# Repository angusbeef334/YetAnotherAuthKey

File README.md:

# YetAnotherAuthKey
A Raspberry Pi RP2354 based PCB that can be flashed with the [pico-fido](https://github.com/polhenarejos/pico-fido) firmware to act as a security key similar to Yubikey, because Yubikeys are expensive and I'm broke.

Made for Hack Club [Blueprint](https://blueprint.hackclub.com)

KiCad 9 format, all of the symbol/footprint libraries should be included in the repo. 

RP2350 and related components symbols/footprints were obtained from [Raspberry Pi](https://datasheets.raspberrypi.com/rp2350/Minimal-KiCAD.zip).

LCSC bom (most of these have MOQs)
| Id | Designator                                 | Footprint                                            | Quantity | Designation      | LCSC Part Number | Ext Price USD |
|----|--------------------------------------------|------------------------------------------------------|----------|------------------|------------------|---------------|
| 1  | C8,C12,C10,C11,C17,C15,C19,C18,C14,C16,C13 | C_0402_1005Metric                                    | 11       | 100n             | C1525            | 0.12          |
| 2  | C1,C2                                      | C_0603_1608Metric                                    | 2        | 10u              | C19702           | 0.29          |
| 3  | SW1                                        | SW_Push_SPST_NO_Alps_SKRK                            | 1        | SW_Push          | C115357          | 0.64          |
| 4  | C6,C9,C7,C5                                | C_0402_1005Metric                                    | 4        | 4.7u             | C368809          | 0.31          |
| 5  | U2                                         | SOT-23                                               | 1        | MCP1700x-330xxTT | C39051           | 1.98          |
| 6  | R3,R2                                      | R_0402_1005Metric                                    | 2        | 27               | C138021          | 0.07          |
| 7  | Y1                                         | Crystal_SMD_3225-4Pin_3.2x2.5mm                      | 1        | ABM8-272-T3      | C20625731        | 1.77          |
| 8  | J1                                         | USB_A_Molex_48037-2200_Horizontal                    | 1        | USB_A            | C2681564         | 0.65          |
| 9  | L1                                         | C_0402_1005Metric                                    | 1        | 3.3u             | C51412           | 0.9           |
| 10 | R4,R5                                      | R_0402_1005Metric                                    | 2        | 1k               | C106235          | 0.06          |
| 11 | R6                                         | R_0402_1005Metric                                    | 1        | 33               | C138002          | 0.07          |
| 12 | U1                                         | RP2350-QFN-60-1EP_7x7_P0.4mm_EP3.4x3.4mm_ThermalVias | 1        | RP2350_60QFN     | C41378174        | 2.49          |
| 13 | C3,C4                                      | C_0402_1005Metric                                    | 2        | 15p              | C86285           | 0.29          |

Total: 9.64 USD

PCB:
14.45 mm* 34.35 mm, green soldermask, leadfree HASL - 3.3 USD + 3 USD stencil

Total: 16 USD + shipping

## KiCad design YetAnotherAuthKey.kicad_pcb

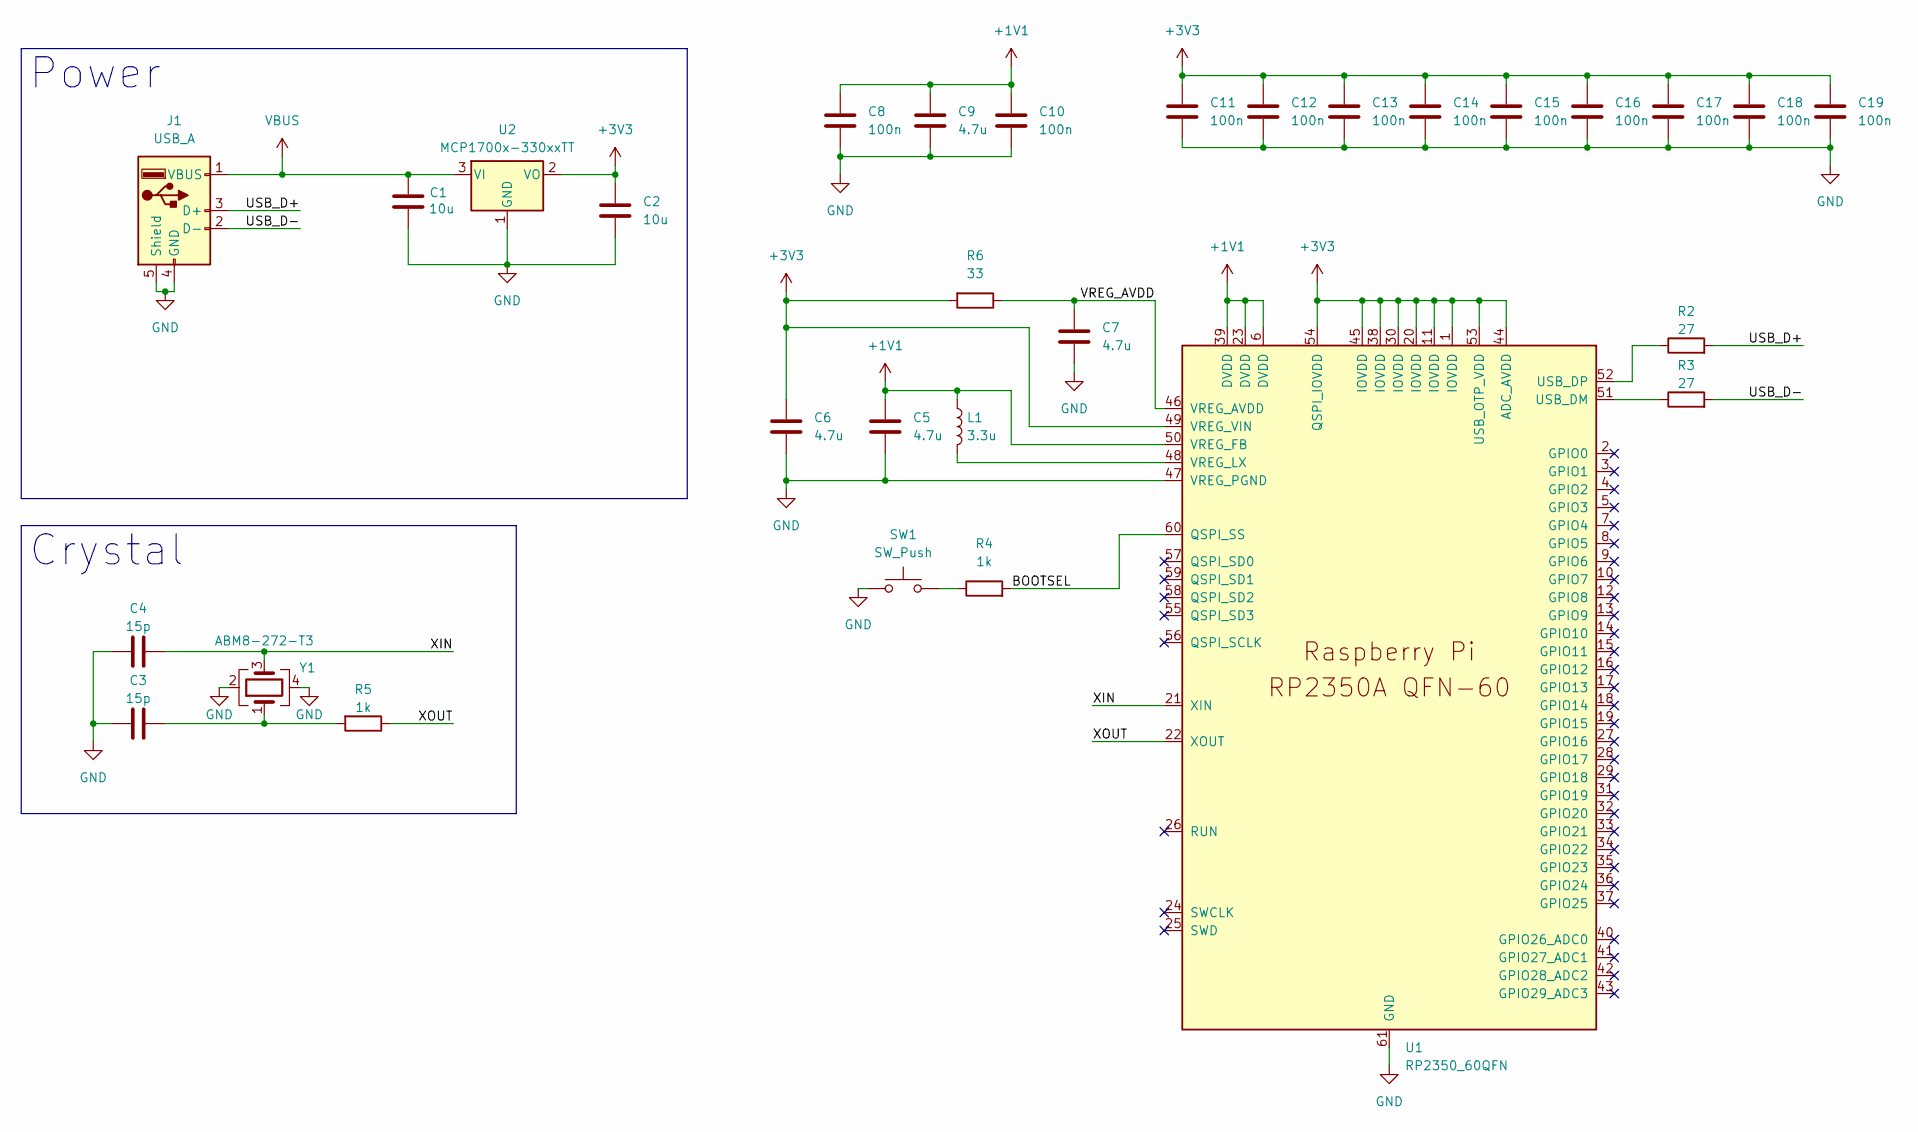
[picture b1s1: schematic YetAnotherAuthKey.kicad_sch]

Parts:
C1, C2: 10u; C_0603_1608Metric
C3, C4: 15p; C_0402_1005Metric
C5, C6, C7, C9: 4.7u; C_0402_1005Metric
C8, C10, C11, C12, C13, C14, C15, C16, C17, C18, C19: 100n; C_0402_1005Metric
J1: USB_A; USB_A_Molex_48037-2200_Horizontal
L1: 3.3u; C_0402_1005Metric
R2, R3: 27; R_0402_1005Metric
R4, R5: 1k; R_0402_1005Metric
R6: 33; R_0402_1005Metric
SW1: SW_Push; SW_Push_SPST_NO_Alps_SKRK
U1: RP2350_60QFN; RP2350-QFN-60-1EP_7x7_P0.4mm_EP3.4x3.4mm_ThermalVias
U2: MCP1700x-330xxTT; SOT-23
Y1: ABM8-272-T3; Crystal_SMD_3225-4Pin_3.2x2.5mm

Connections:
+1V1: C5.1, C8.1, C9.1, C10.1, L1.1, U1.6 (DVDD), U1.23 (DVDD), U1.39 (DVDD), U1.50 (VREG_FB)
+3V3: C2.1, C6.1, C11.1, C12.1, C13.1, C14.1, C15.1, C16.1, C17.1, C18.1, C19.1, R6.2, U1.1 (IOVDD), U1.11 (IOVDD), U1.20 (IOVDD), U1.30 (IOVDD), U1.38 (IOVDD), U1.44 (ADC_AVDD), U1.45 (IOVDD), U1.49 (VREG_VIN), U1.53 (USB_OTP_VDD), U1.54 (QSPI_IOVDD), U2.2 (VO)
/BOOTSEL: R4.2, U1.60 (QSPI_SS)
/USB_D+: J1.3 (D+), R2.2
/USB_D-: J1.2 (D-), R3.2
/VREG_AVDD: C7.1, R6.1, U1.46 (VREG_AVDD)
/XIN: C4.1, U1.21 (XIN), Y1.3
/XOUT: R5.1, U1.22 (XOUT)
GND: C1.1, C2.2, C3.2, C4.2, C5.2, C6.2, C7.2, C8.2, C9.2, C10.2, C11.2, C12.2, C13.2, C14.2, C15.2, C16.2, C17.2, C18.2, C19.2, J1.4 (GND), J1.5 (Shield), SW1.1, U1.47 (VREG_PGND), U1.61 (GND), U2.1 (GND), Y1.2, Y1.4
unnamed: C3.1, R5.2, Y1.1
unnamed: R4.1, SW1.2
unnamed: R3.1, U1.51 (USB_DM)
unnamed: R2.1, U1.52 (USB_DP)
unnamed: L1.2, U1.48 (VREG_LX)
VBUS: C1.2, J1.1 (VBUS), U2.3 (VI)

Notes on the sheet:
Crystal
Power

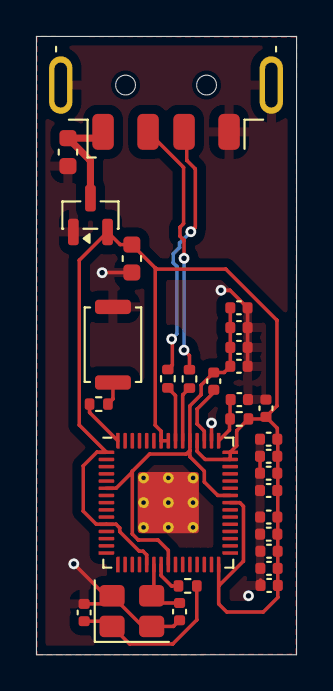
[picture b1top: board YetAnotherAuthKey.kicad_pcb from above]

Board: 2 copper layers, 14.4 x 34.3 mm, 30 parts (0 on the bottom side), 15 nets.

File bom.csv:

"Id";"Designator";"Footprint";"Quantity";"Designation";"Supplier and ref";
1;"C8,C12,C10,C11,C17,C15,C19,C18,C14,C16,C13";"C_0402_1005Metric";11;"100n";;;
2;"C1,C2";"C_0603_1608Metric";2;"10u";;;
3;"SW1";"SW_Push_SPST_NO_Alps_SKRK";1;"SW_Push";;;
4;"C6,C9,C7,C5";"C_0402_1005Metric";4;"4.7u";;;
5;"U2";"SOT-23";1;"MCP1700x-330xxTT";;;
6;"R3,R2";"R_0402_1005Metric";2;"27";;;
7;"Y1";"Crystal_SMD_3225-4Pin_3.2x2.5mm";1;"ABM8-272-T3";;;
8;"J1";"USB_A_Molex_48037-2200_Horizontal";1;"USB_A";;;
9;"L1";"C_0402_1005Metric";1;"3.3u";;;
10;"R4,R5";"R_0402_1005Metric";2;"1k";;;
11;"R6";"R_0402_1005Metric";1;"33";;;
12;"U1";"RP2350-QFN-60-1EP_7x7_P0.4mm_EP3.4x3.4mm_ThermalVias";1;"RP2350_60QFN";;;
13;"C3,C4";"C_0402_1005Metric";2;"15p";;;

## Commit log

2025-10-06 place components
2025-10-07 clean schematic
2025-10-07 add missing grounds
2025-11-01 finish pcb
2025-11-01 add bom
2025-11-01 add lcsc parts info
2025-11-01 fix structure, add cad model
2025-11-11 add costs
